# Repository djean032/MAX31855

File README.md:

# MAX31855

## Project Description
A solution to control and monitor four thermocouples using the MAX31855 Thermocouple Amplifier.

## Contents
- Arduino Sketch
- Custom MAX31855 Library
- KICAD Generated Schematic and PCB
- Test Data

## Arduino Sketch

The Arduino sketch is designed to print both to a serial monitor on a PC and a LCD screen that is mounted on the device.

## MAX31855 Library

Custom library that creates a class instance of each thermocouple amplifier and provides functions to read data, check errors, and do a rational polynomial caluclation to accurately determine the temperature. Additionally a weighted average is used to filter the signal, resulting in a significantly smoothed reading.

The initial form of this library uses a switch statement to select the proper conversion function based on thermocouple type, of which only type 'T' and 'K' are currently supported. Additional types will be added in the future, so this library can be universally used across all thermocouple and MAX31855 types.

## Schematic

## Circuit Features

#### Overview

The circuit consists of four MAX31855 thermocouple amplifiers that are connected to an Arduino Micro. The Arduino Micro is connected to the the thermocouple amplifiers via SPI, utilizing the SCK, MISO, and CS lines. The Arduino also communicates the data to a PC via serial while also displaying it on an onboard LCD.

#### MAX31855 Idiosyncrasies

The MAX31855 transmits a cold-junction compensated thermocouple temperature, a cold-junction temperature (from a thermistor), and several fault checks over 32 bits. The first 14 bits are the cold-junction compensated thermocouple temperature, the next 12 bits are the cold-junction temperature, and the rest of the bits are either reserved bits or denote various fault checks.

The MAX31855 uses a linear conversion to convert the thermocouple voltage to a temperature. Specifically the type 'T' version uses a factor of $52.18 \frac{\mu V}{\textdegree C}$, which shows significant deviations at room temperature from tabulated values. For this application, this is not a suitable conversion method, so a rational polynomial function was employed in software to more accurately  model the thermocouple response. The basic steps are to convert the measured thermocouple temperature to a voltage using the linear relationship stated in the datasheet. Then a switch statement is used to slect the type of chip to determine the appropriate coefficients for the rational polynomial function. Finally, the thermocouple voltage and coefficients are used in the rational polynomial function to compute a corrected temperature. This was tested at several temperatures and provides an acceptable level of accuracy.

#### Data Transfer

The data is simultaneously displayed on an LCD screen and transmitted to a PC via USB, where it is read into our lab's LabView program used to control our spectrometer. The data is "filtered" using a weighted average that takes a weighted average of the previous value with the current value. This weight can be adjusted via software. 30% of the previous value seems to be a sweet spot between data smoothing and quick response time.

#### Power Supply

The device is powered via a 9V external AC to DC power supply. In our current application, we have an approximately 15m USB cable, which is triple the specification for USB 2.0. 

#### Miscellaneous

The MAX31855 requires 3.3V to operate, while the Arduino Micro operates at 5V, so two bi-directional level shifters were used for the data and power lines for the thermocouple amplifiers.

## PCB

## Evaluation

#### Summary
Overall, once the rational polynomial function and filtering was added, the performance was adequate for our lab's needs. It successfully reads temperatures from boiling water down to cryogenic temperatures used in our lab's spectrometer.

#### Data
|        Cooling Bath         | Measured Temperature ($\degree C$) | Theoretical Value ($\degree C$) |
|:---------------------------:|:----------------------------------:|:-------------------------------:|
|          Ice Water          |                -2.0                |                0                |
|      Dry Ice + Acetone      |               -79.4                |               -78               |
|   Acetone + liquid N$^2$    |               -95.0                |               -94               |
| n-pentane +    liquid N$^2$ |              -133.5               |              -131               |
|        liquid N$^2$         |                -200                |              -196               |
|        Boiling Water        |               98.0                |         100                        |

Overall, the data matches very well with the theoretical values, within 2% error for all the cooling baths. The ice water and boiling water were done with tap water, so that is the likely source for the deviation there.

#### Future
Further improvements will be implemented in v2. These include capacitors to clean up the power supply and capacitors added on to the VCC and GND lines of the thermocouple amplifiers to prevent coupling of the data and power supply lines.

## v2 To-Do List
- Proper power supply design
	- Add appropriate capacitors to the input to reduce noise
- Add small capacitors to the VCC and GND lines of the thermocouple amplifiers to prevent coupling of the signal and the power lines.
- Transmit data over something other than USB

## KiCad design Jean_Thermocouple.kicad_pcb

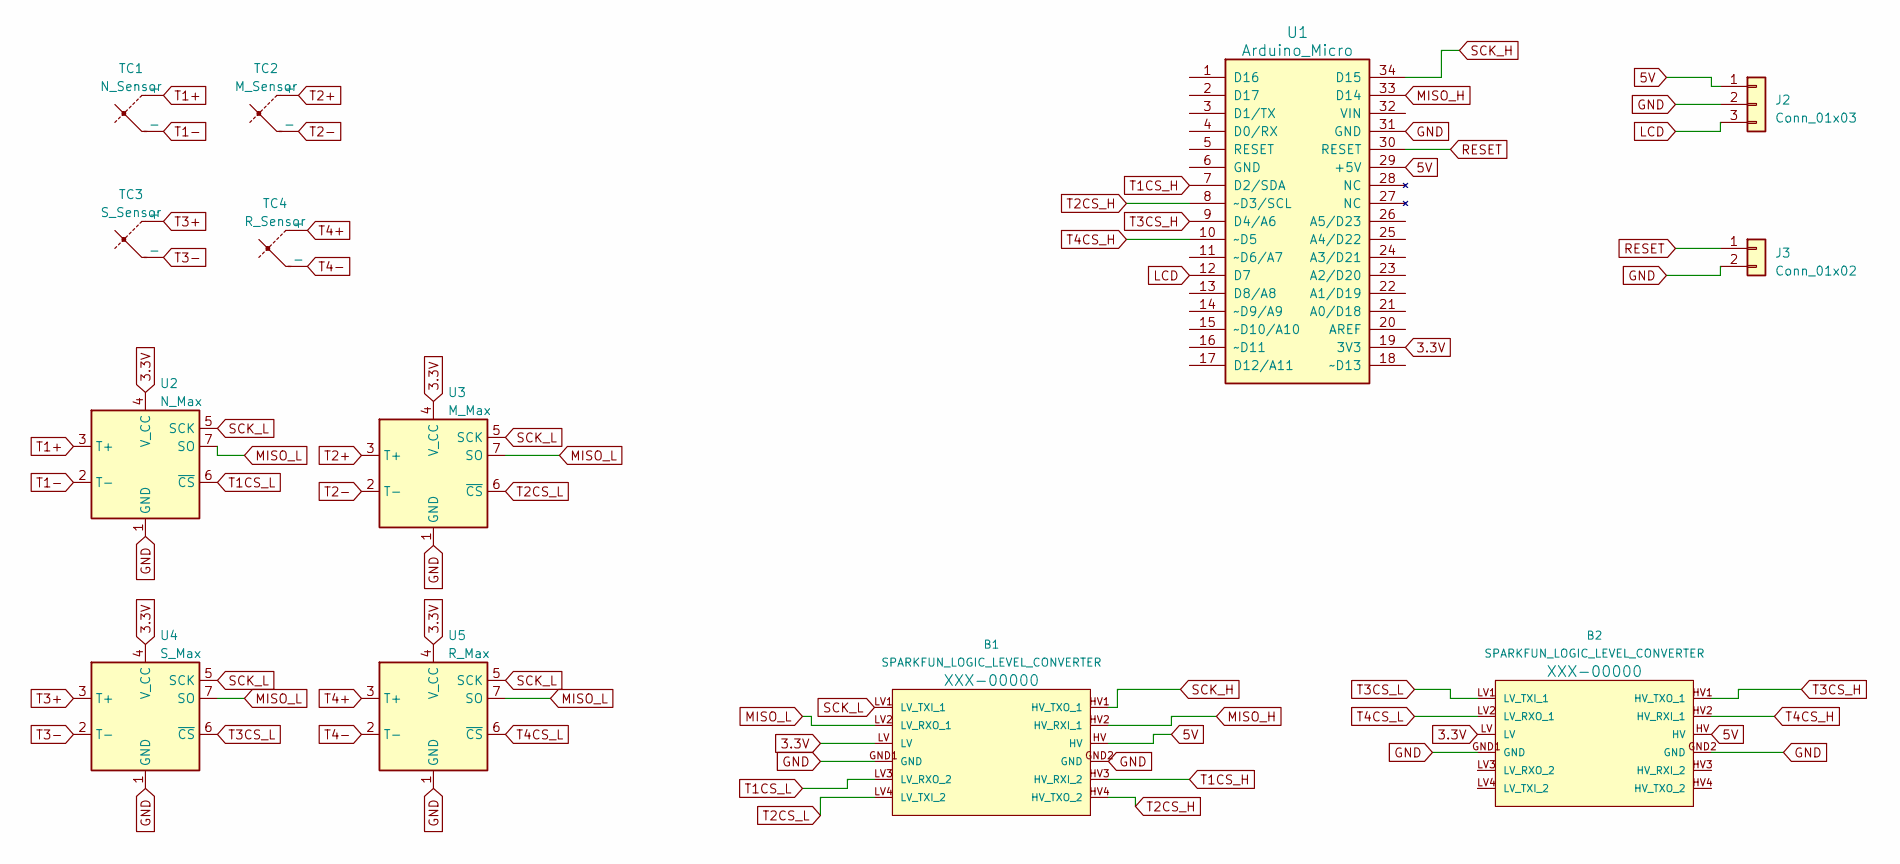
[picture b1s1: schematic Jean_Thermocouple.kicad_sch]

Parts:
B1, B2: SPARKFUN_LOGIC_LEVEL_CONVERTER
J2: Conn_01x03; PinHeader_1x03_P2.54mm_Vertical
J3: Conn_01x02; PinHeader_1x02_P2.54mm_Vertical
TC1: N_Sensor; PinHeader_1x02_P2.54mm_Vertical
TC2: M_Sensor; PinHeader_1x02_P2.54mm_Vertical
TC3: S_Sensor; PinHeader_1x02_P2.54mm_Vertical
TC4: R_Sensor; PinHeader_1x02_P2.54mm_Vertical
U1: Arduino_Micro
U2: N_Max; SOIC-8_3.9x4.9mm_P1.27mm
U3: M_Max; SOIC-8_3.9x4.9mm_P1.27mm
U4: S_Max; SOIC-8_3.9x4.9mm_P1.27mm
U5: R_Max; SOIC-8_3.9x4.9mm_P1.27mm

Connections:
3.3V: B1.LV, B2.LV, U1.19 (3V3), U2.4 (V_CC), U3.4 (V_CC), U4.4 (V_CC), U5.4 (V_CC)
5V: B1.HV, B2.HV, J2.1, U1.29 (+5V)
GND: B1.GND1 (GND), B1.GND2 (GND), B2.GND1 (GND), B2.GND2 (GND), J2.2, J3.2, U1.31 (GND), U2.1 (GND), U3.1 (GND), U4.1 (GND), U5.1 (GND)
LCD: J2.3, U1.12 (D7)
MISO_H: B1.HV2 (HV_RXI_1), U1.33 (D14)
MISO_L: B1.LV2 (LV_RXO_1), U2.7 (SO), U3.7 (SO), U4.7 (SO), U5.7 (SO)
RESET: J3.1, U1.30 (RESET)
SCK_H: B1.HV1 (HV_TXO_1), U1.34 (D15)
SCK_L: B1.LV1 (LV_TXI_1), U2.5 (SCK), U3.5 (SCK), U4.5 (SCK), U5.5 (SCK)
T1+: TC1.1 (+), U2.3 (T+)
T1-: TC1.2 (-), U2.2 (T-)
T1CS_H: B1.HV3 (HV_RXI_2), U1.7 (D2/SDA)
T1CS_L: B1.LV3 (LV_RXO_2), U2.6 (~CS)
T2+: TC2.1 (+), U3.3 (T+)
T2-: TC2.2 (-), U3.2 (T-)
T2CS_H: B1.HV4 (HV_TXO_2), U1.8 (~D3/SCL)
T2CS_L: B1.LV4 (LV_TXI_2), U3.6 (~CS)
T3+: TC3.1 (+), U4.3 (T+)
T3-: TC3.2 (-), U4.2 (T-)
T3CS_H: B2.HV1 (HV_TXO_1), U1.9 (D4/A6)
T3CS_L: B2.LV1 (LV_TXI_1), U4.6 (~CS)
T4+: TC4.1 (+), U5.3 (T+)
T4-: TC4.2 (-), U5.2 (T-)
T4CS_H: B2.HV2 (HV_RXI_1), U1.10 (~D5)
T4CS_L: B2.LV2 (LV_RXO_1), U5.6 (~CS)

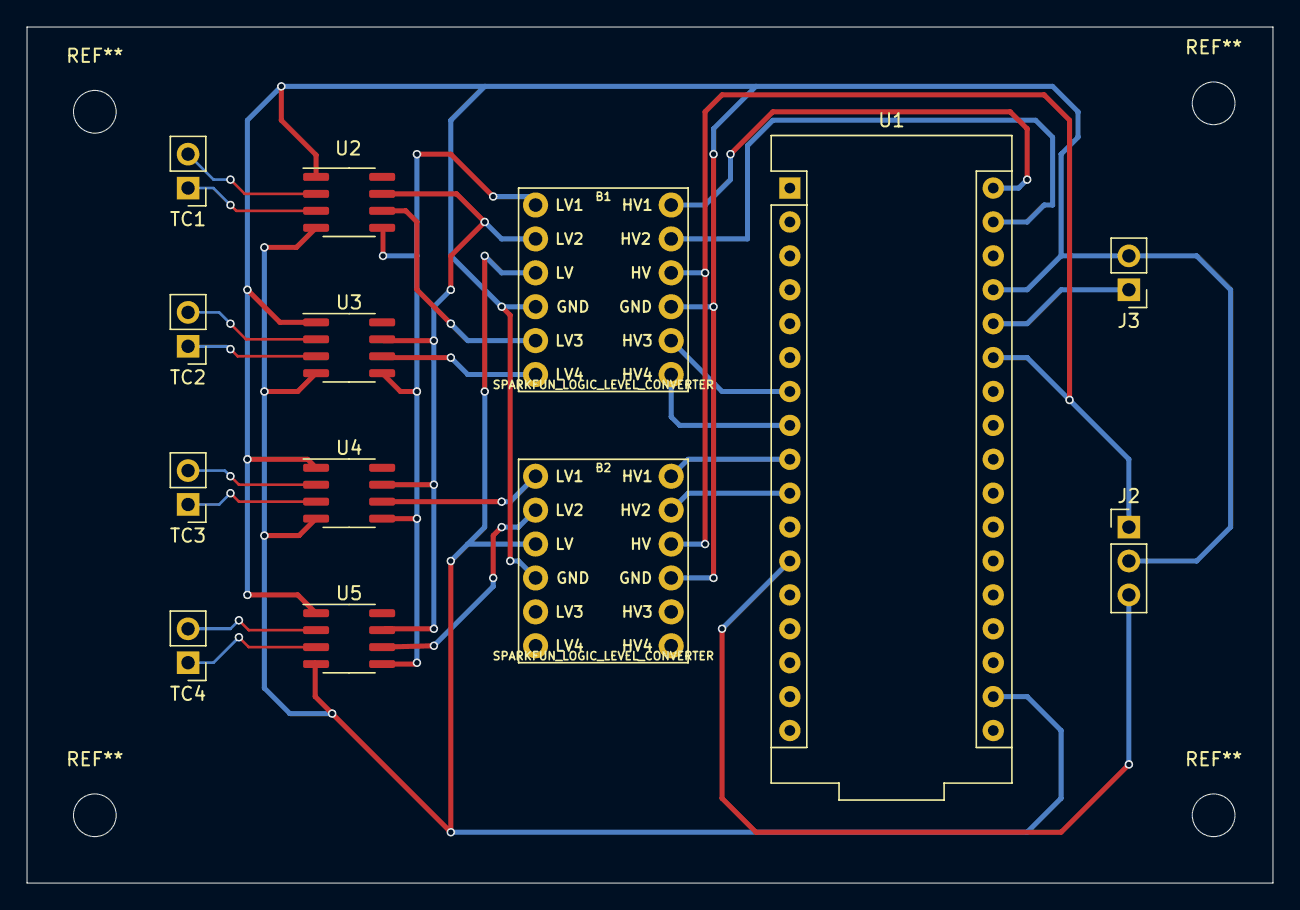
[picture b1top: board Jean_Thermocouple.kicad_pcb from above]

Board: 2 copper layers, 93.3 x 64.1 mm, 13 parts (0 on the bottom side), 25 nets.

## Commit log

2023-05-07 Added PCB and Schematic
2023-05-07 Fixed type issues
2023-05-11 Fixed some data register duplication issues
2023-05-11 Fixed miscellaneous bugs
2023-05-12 fixed loop errors
2023-05-13 reorganization
